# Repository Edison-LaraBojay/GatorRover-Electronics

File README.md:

# GatorRover-Electronics
Everything electronics for gator rover...

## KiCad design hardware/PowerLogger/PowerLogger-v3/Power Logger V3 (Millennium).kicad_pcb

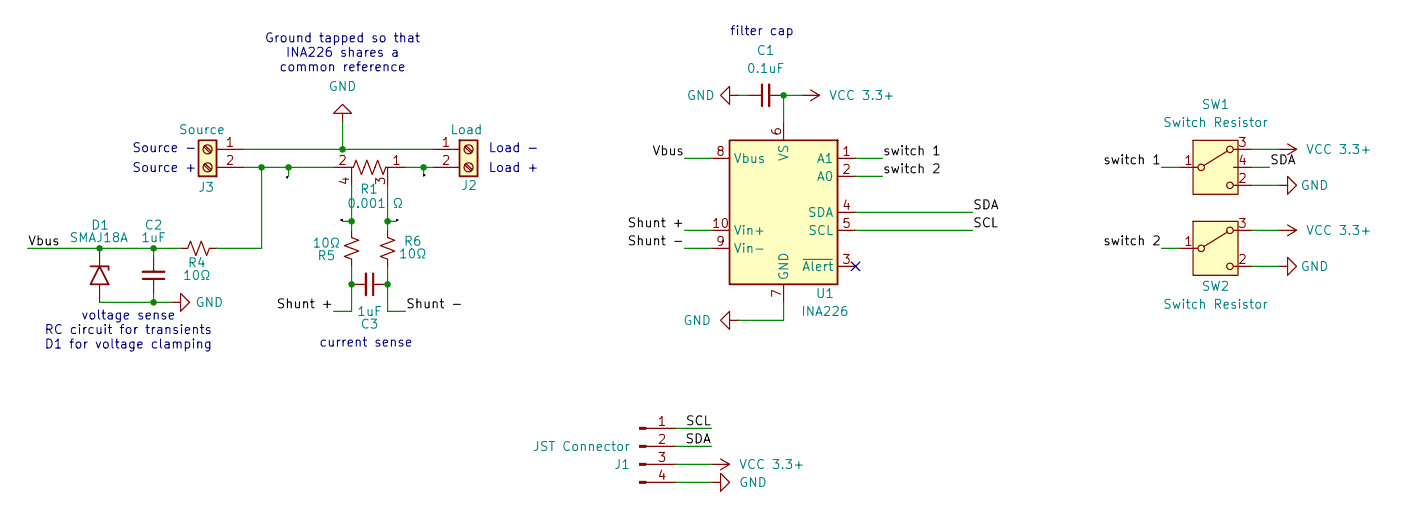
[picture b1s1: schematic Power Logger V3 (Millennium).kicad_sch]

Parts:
C1: 0.1uF; C_0603_1608Metric_Pad1.08x0.95mm_HandSolder
C2, C3: 1uF; C_0603_1608Metric_Pad1.08x0.95mm_HandSolder
D1: SMAJ18A; D_SMA
J1: JST Connector; JST_PH_S4B-PH-K_1x04_P2.00mm_Horizontal
J2: Load; Untitled_1
J3: Source; Untitled
R1: 0.001 Ω; R_2512_6332Metric_Pad1.40x3.35mm_HandSolder
R4, R5, R6: 10Ω; R_0603_1608Metric_Pad0.98x0.95mm_HandSolder
SW1, SW2: Switch Resistor; switch resistor
U1: INA226; TSSOP-10_3x3mm_P0.5mm

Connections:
/Load_VDD: J2.2, R1.1
/SCL: J1.1, U1.5 (SCL)
/SDA: J1.2, SW1.4, U1.4 (SDA)
/Shunt +: C3.2, R5.1, U1.10 (Vin+)
/Shunt -: C3.1, R6.2, U1.9 (Vin-)
/Source_VDD: J3.2 (Pin_1), R1.2, R4.2
/Vbus: C2.2, D1.1 (A1), R4.1, U1.8 (Vbus)
/switch 1: SW1.1 (B), U1.1 (A1)
/switch 2: SW2.1 (B), U1.2 (A0)
/to filter +: R1.4, R5.2
/to filter -: R1.3, R6.1
GND: C1.1, C2.1, D1.2 (A2), J1.4, J2.1, J3.1 (Pin_2), SW1.2 (C), SW2.2 (C), U1.7 (GND)
VCC 3.3+: C1.2, J1.3, SW1.3 (A), SW2.3 (A), U1.6 (VS)

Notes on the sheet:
Ground tapped so that INA226 shares a common reference
Source -
Source +
filter cap
Load +
current sense
Load -
voltage sense RC circuit for transients D1 for voltage clamping

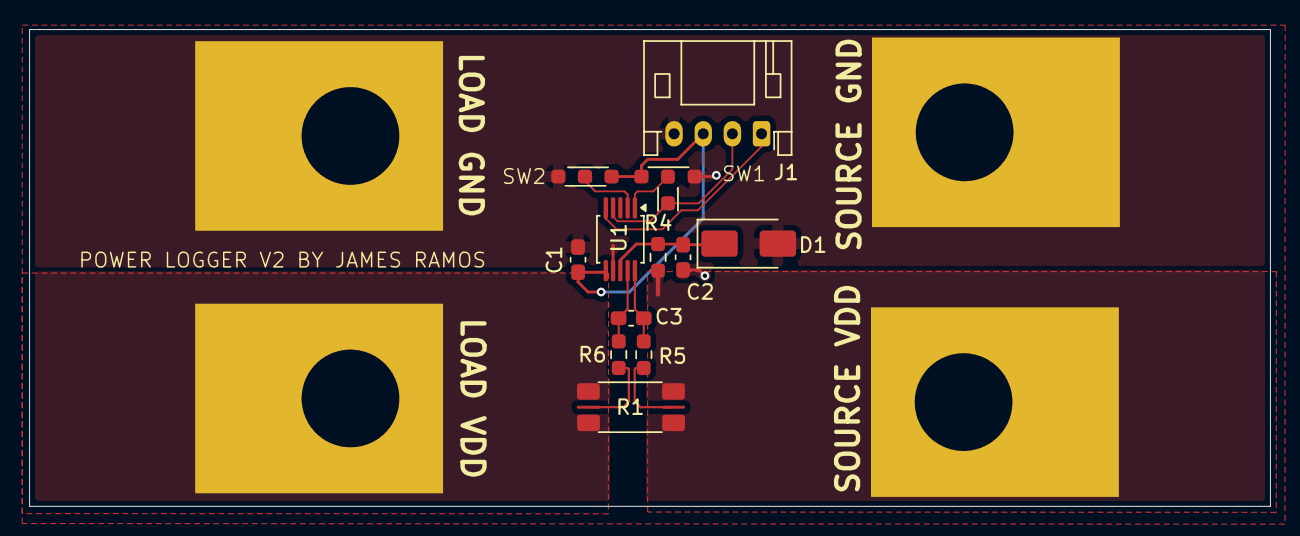
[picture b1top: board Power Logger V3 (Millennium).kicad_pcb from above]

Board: 2 copper layers, 85.1 x 32.7 mm, 14 parts (0 on the bottom side), 13 nets.

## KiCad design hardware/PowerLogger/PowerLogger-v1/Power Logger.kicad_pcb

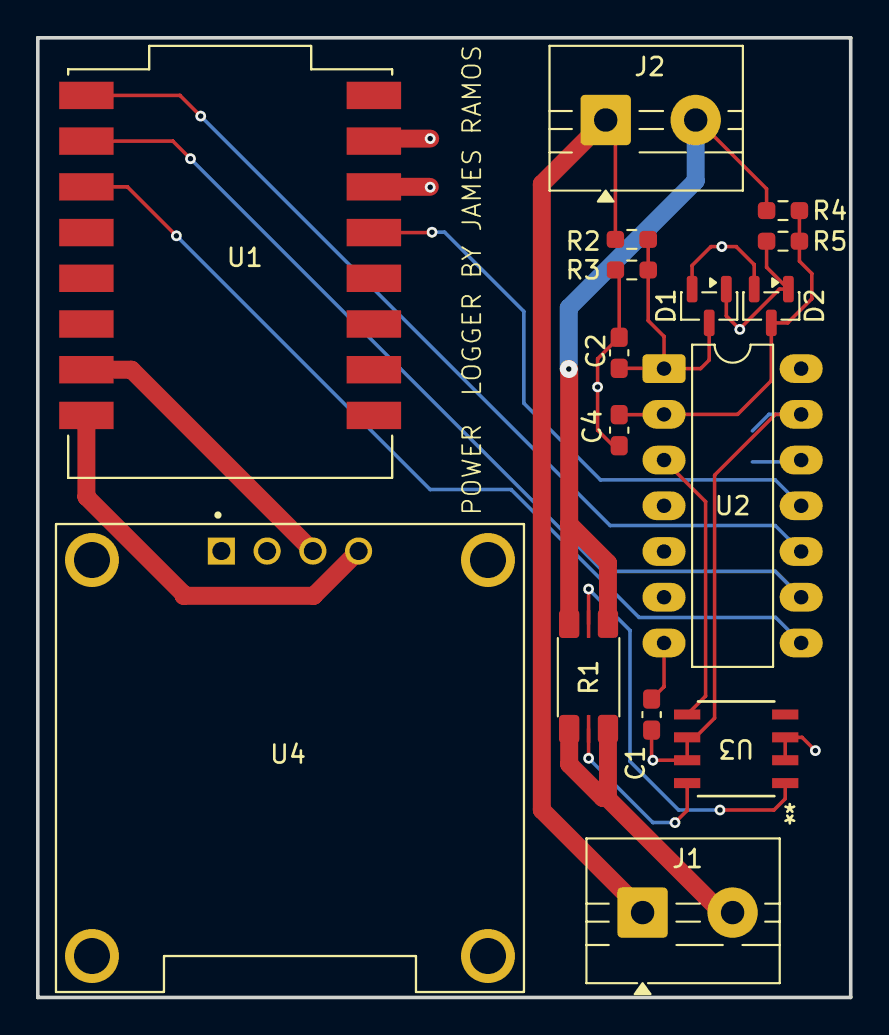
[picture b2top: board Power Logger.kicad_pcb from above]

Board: 4 copper layers, 45.2 x 53.3 mm, 17 parts (1 on the bottom side), 16 nets.

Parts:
C1, C2, C3, C4: 0.1 µF; C_0603_1608Metric_Pad1.08x0.95mm_HandSolder
D1, D2: BAT54S; SOT-23
J1: Source A1 A2; TerminalBlock_MaiXu_MX126-5.0-02P_1x02_P5.00mm
J2: Load B1 B2; TerminalBlock_MaiXu_MX126-5.0-02P_1x02_P5.00mm
R1: 5m; R_2512_6332Metric_Pad1.40x3.35mm_HandSolder
R2, R4: 10k; R_0603_1608Metric_Pad0.98x0.95mm_HandSolder
R3, R5: 2.2k; R_0603_1608Metric_Pad0.98x0.95mm_HandSolder
U1: ESP32-C3_SUPERMINI_SMD; MODULE_ESP32-C3_SUPERMINI
U2: MCP3204; DIP-14_W7.62mm_LongPads
U3: INA240A1D; D8_TEX
U4: DM-OLED096-636; MODULE_DM-OLED096-636

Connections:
+3.3V: C1.2, C3.1, D1.2 (K), D2.2 (K), U1.3.3 (3V3), U2.13 (Vref), U2.14 (Vdd), U3.6 (VS), U3.7 (REF1), U4.2 (VCC_IN)
/ADC1: C2.1, D1.3 (COM), R2.2, R3.1, U2.1 (CH0)
/ADC2: C4.1, D2.3 (COM), R4.2, R5.1, U2.2 (CH1)
/CS/SHDN: U1.7 (GPIO7), U2.8 (~CS/SHDN)
/Current Out: U2.3 (CH2), U3.5 (OUT)
/MISO: U1.5 (GPIO5), U2.10 (Dout)
/MOSI: U1.6 (GPIO6), U2.9 (Din)
/SCK: U1.4 (GPIO4), U2.11 (CLK)
/SCL: U1.20 (GPIO20), U4.3 (SCL)
/SDA: U1.21 (GPIO21), U4.4 (SDA)
/Shunt In+: R1.3, U3.8 (IN+)
/Shunt In-: R1.4, U3.1 (IN-)
GND: C1.1, C2.2, C3.2, C4.2, D1.1 (A), D2.1 (A), R3.2, R5.2, U1.G (GND), U2.7 (DGND), U2.12 (AGND), U3.2 (GND), U3.3 (REF2), U4.1 (GND)
unnamed: J1.2 (Pin_1), R1.1
unnamed: J1.1 (Pin_2), J2.1, R2.1
unnamed: J2.2, R1.2, R4.1

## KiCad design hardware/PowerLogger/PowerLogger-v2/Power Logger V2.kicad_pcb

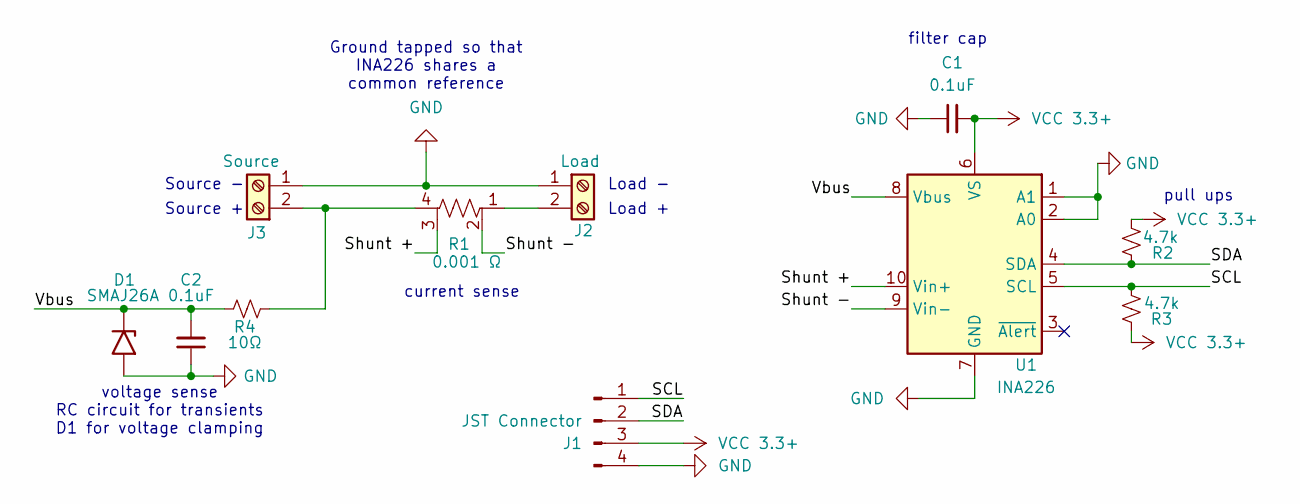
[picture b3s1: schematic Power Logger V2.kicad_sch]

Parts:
C1, C2: 0.1uF; C_0603_1608Metric_Pad1.08x0.95mm_HandSolder
D1: SMAJ26A; D_SMA
J1: JST Connector; JST_PH_S4B-PH-K_1x04_P2.00mm_Horizontal
J2: Load; PowerLogger-Load
J3: Source; PowerLogger-Source
R1: 0.001 Ω; R_Shunt_Vishay_WSK2512_6332Metric_T2.21mm
R2, R3: 4.7k; R_0603_1608Metric_Pad0.98x0.95mm_HandSolder
R4: 10Ω; R_0603_1608Metric_Pad0.98x0.95mm_HandSolder
U1: INA226; TSSOP-10_3x3mm_P0.5mm

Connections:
/SCL: J1.1, R3.2, U1.5 (SCL)
/SDA: J1.2, R2.1, U1.4 (SDA)
/Shunt +: R1.3, U1.10 (Vin+)
/Shunt -: R1.2, U1.9 (Vin-)
/Vbus: C2.2, D1.1 (A1), R4.1, U1.8 (Vbus)
GND: C1.1, C2.1, D1.2 (A2), J1.4, J2.1, J3.1 (Pin_2), U1.1 (A1), U1.2 (A0), U1.7 (GND)
unnamed: J2.2, R1.1
unnamed: J3.2 (Pin_1), R1.4, R4.2
VCC 3.3+: C1.2, J1.3, R2.2, R3.1, U1.6 (VS)

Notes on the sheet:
Load -
Ground tapped so that INA226 shares a common reference
pull ups
current sense
voltage sense RC circuit for transients D1 for voltage clamping
filter cap
Source +
Load +
Source -

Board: 4 copper layers, 11 parts (0 on the bottom side), 9 nets, no tracks yet.

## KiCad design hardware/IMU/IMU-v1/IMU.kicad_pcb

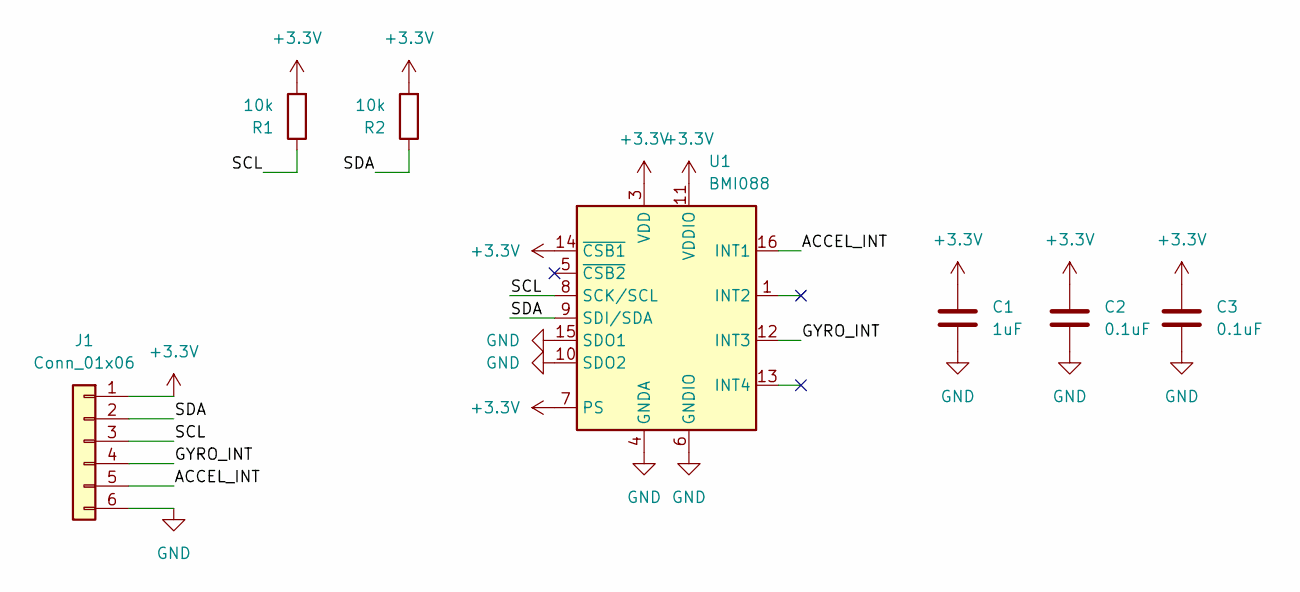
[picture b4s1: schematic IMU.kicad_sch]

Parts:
C1: 1uF; C_0805_2012Metric_Pad1.18x1.45mm_HandSolder
C2, C3: 0.1uF; C_0805_2012Metric_Pad1.18x1.45mm_HandSolder
J1: Conn_01x06; JST_PH_S6B-PH-K_1x06_P2.00mm_Horizontal
R1, R2: 10k; R_0805_2012Metric_Pad1.20x1.40mm_HandSolder
U1: BMI088; Bosch_LGA-16_4.5x3mm_P0.5mm_LayoutBorder7x1y_ClockwisePinNu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

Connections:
+3.3V: C1.1, C2.1, C3.1, J1.1, R1.2, R2.2, U1.3 (VDD), U1.7 (PS), U1.11 (VDDIO), U1.14 (~CSB1)
/ACCEL_INT: J1.5, U1.16 (INT1)
/GYRO_INT: J1.4, U1.12 (INT3)
/SCL: J1.3, R1.1, U1.8 (SCK/SCL)
/SDA: J1.2, R2.1, U1.9 (SDI/SDA)
GND: C1.2, C2.2, C3.2, J1.6, U1.2 (GNDA), U1.4 (GNDA), U1.6 (GNDIO), U1.10 (SDO2), U1.15 (SDO1)

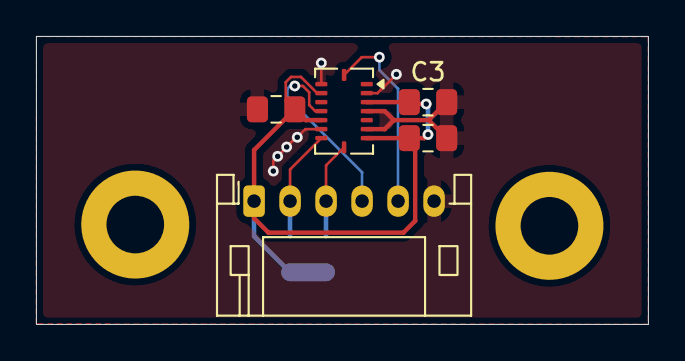
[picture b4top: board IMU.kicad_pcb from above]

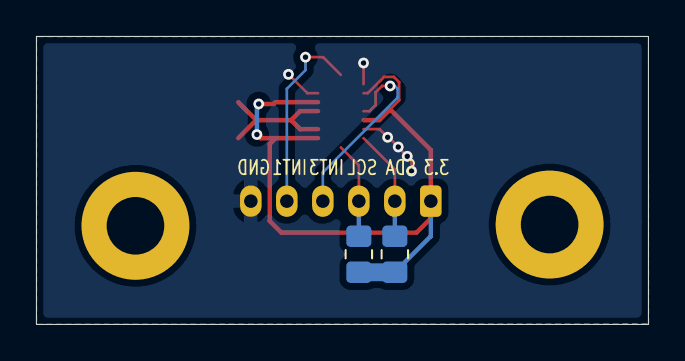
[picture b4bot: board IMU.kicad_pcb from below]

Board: 2 copper layers, 34.0 x 16.0 mm, 7 parts (2 on the bottom side), 6 nets.
